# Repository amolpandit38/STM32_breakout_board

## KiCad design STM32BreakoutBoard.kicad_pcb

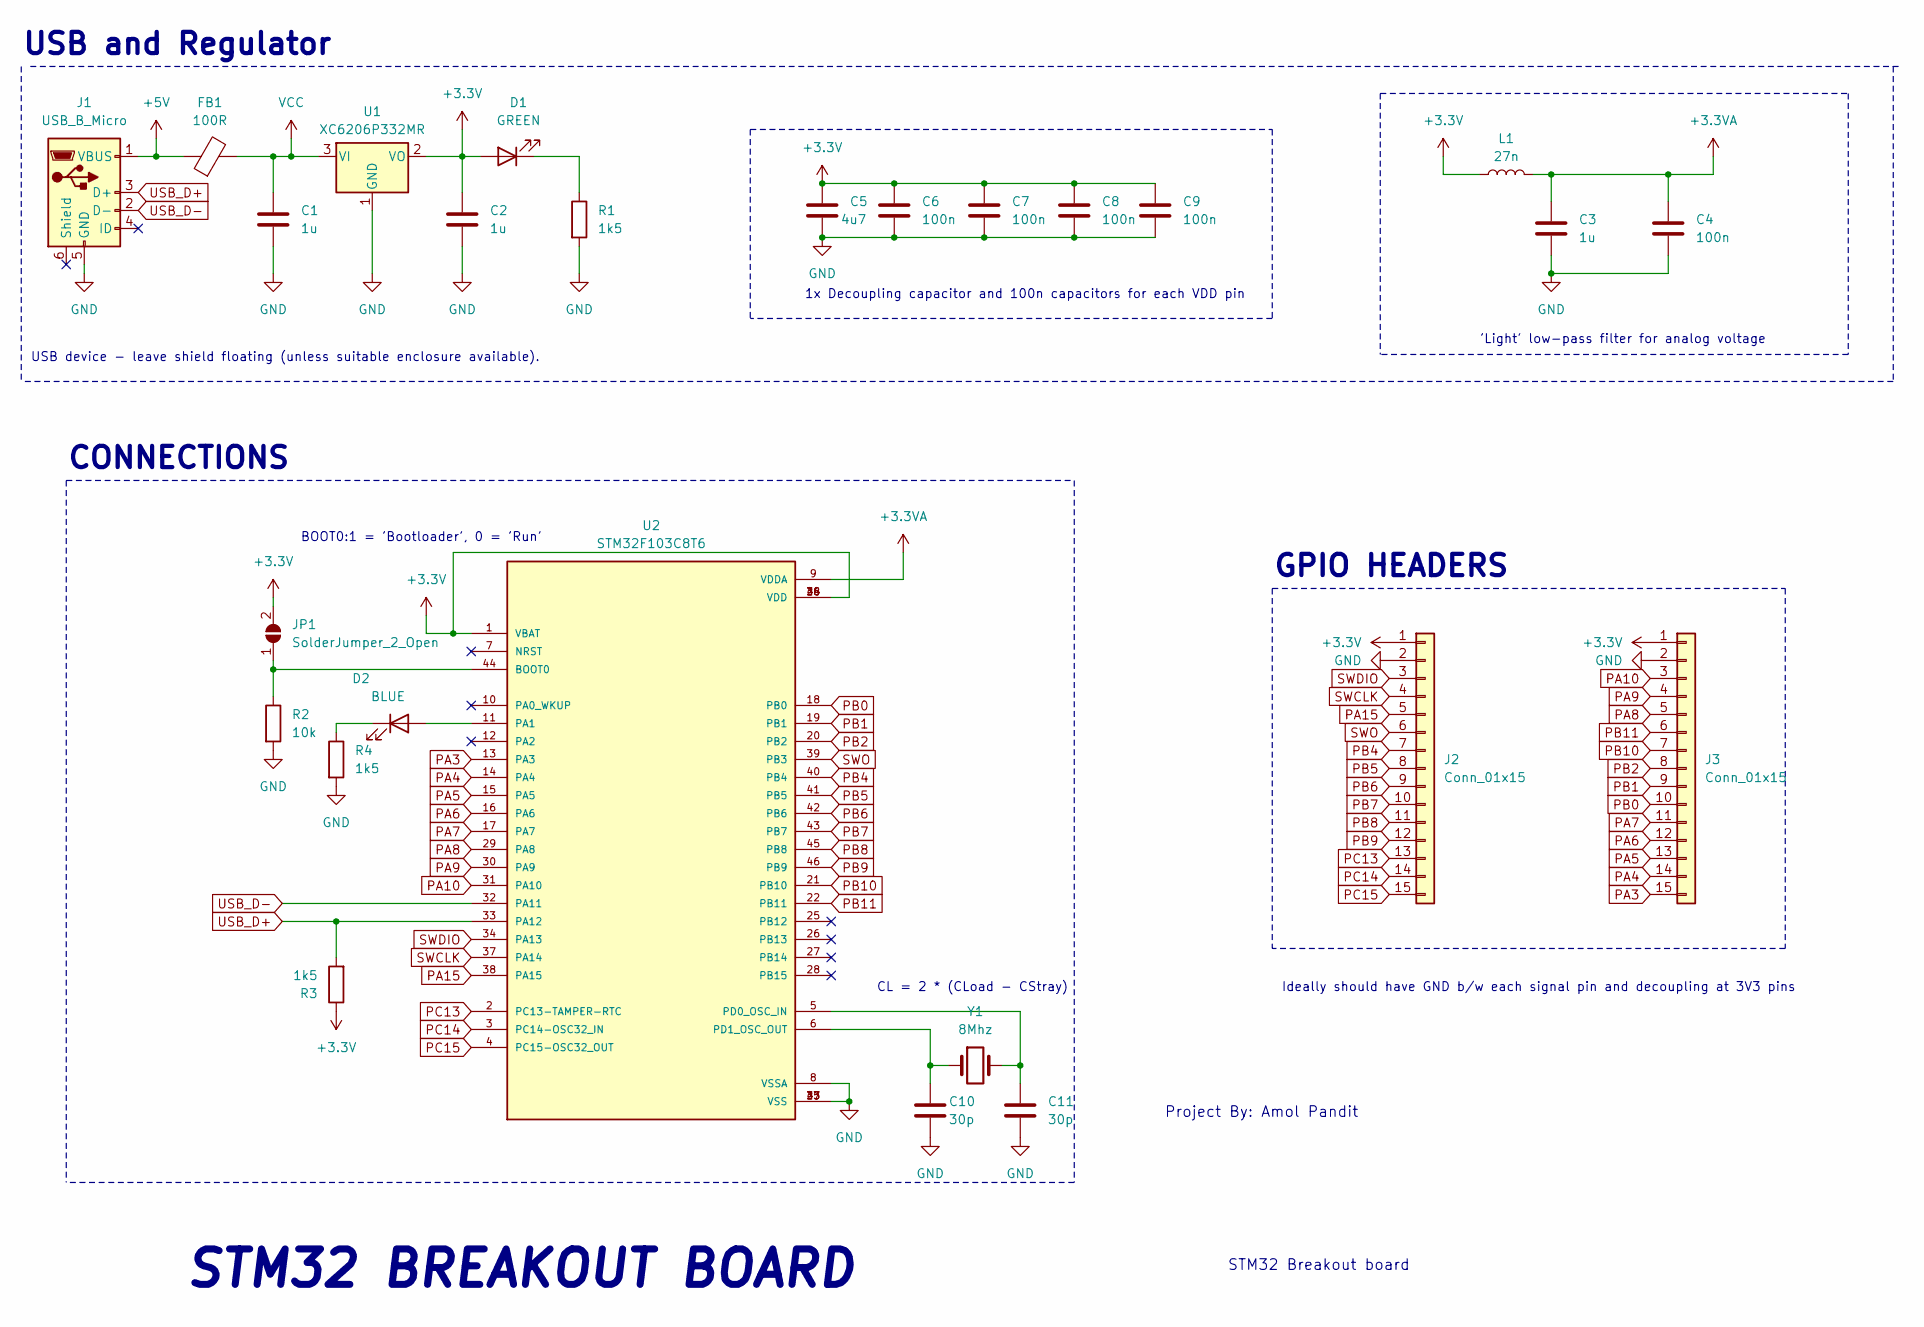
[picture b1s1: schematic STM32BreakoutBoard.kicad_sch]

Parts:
C1, C2, C3: 1u; C_0603_1608Metric
C4, C6, C7, C8, C9: 100n; C_0402_1005Metric
C5: 4u7; C_0603_1608Metric
C10, C11: 30p; C_0402_1005Metric
D1: GREEN; LED_0603_1608Metric
D2: BLUE; LED_0603_1608Metric
FB1: 100R; L_0805_2012Metric
J1: USB_B_Micro; USB_Micro-B_Wuerth_629105150521
J2, J3: Conn_01x15; PinHeader_1x15_P2.54mm_Vertical
JP1: SolderJumper_2_Open; SolderJumper-2_P1.3mm_Open_Pad1.0x1.5mm
L1: 27n; L_0402_1005Metric
R1, R3, R4: 1k5; R_0402_1005Metric
R2: 10k; R_0603_1608Metric
U1: XC6206P332MR; SOT-23-3
U2: STM32F103C8T6; QFP50P900X900X160-48N; PARTREV 10
Y1: 8Mhz; Crystal_SMD_5032-2Pin_5.0x3.2mm

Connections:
+3.3V: C2.1, C5.1, C6.1, C7.1, C8.1, C9.1, D1.2 (A), J2.1, J3.1, JP1.2 (B), L1.1, R3.1, U1.2 (VO), U2.1 (VBAT), U2.24 (VDD), U2.36 (VDD), U2.48 (VDD)
+3.3VA: C3.1, C4.1, L1.2, U2.9 (VDDA)
+5V: FB1.1, J1.1 (VBUS)
GND: C1.2, C2.2, C3.2, C4.2, C5.2, C6.2, C7.2, C8.2, C9.2, C10.2, C11.2, J1.5 (GND), J2.2, J3.2, R1.2, R2.2, R4.2, U1.1 (GND), U2.8 (VSSA), U2.23 (VSS), U2.35 (VSS), U2.47 (VSS)
unnamed: D1.1 (K), R1.1
unnamed: D2.2 (A), U2.11 (PA1)
unnamed: D2.1 (K), R4.1
unnamed: JP1.1 (A), R2.1, U2.44 (BOOT0)
unnamed: C11.1, U2.5 (PD0_OSC_IN), Y1.2
unnamed: C10.1, U2.6 (PD1_OSC_OUT), Y1.1
PA3: J3.15, U2.13 (PA3)
PA4: J3.14, U2.14 (PA4)
PA5: J3.13, U2.15 (PA5)
PA6: J3.12, U2.16 (PA6)
PA7: J3.11, U2.17 (PA7)
PA8: J3.5, U2.29 (PA8)
PA9: J3.4, U2.30 (PA9)
PA10: J3.3, U2.31 (PA10)
PA15: J2.5, U2.38 (PA15)
PB0: J3.10, U2.18 (PB0)
PB1: J3.9, U2.19 (PB1)
PB2: J3.8, U2.20 (PB2)
PB4: J2.7, U2.40 (PB4)
PB5: J2.8, U2.41 (PB5)
PB6: J2.9, U2.42 (PB6)
PB7: J2.10, U2.43 (PB7)
PB8: J2.11, U2.45 (PB8)
PB9: J2.12, U2.46 (PB9)
PB10: J3.7, U2.21 (PB10)
PB11: J3.6, U2.22 (PB11)
PC13: J2.13, U2.2 (PC13-TAMPER-RTC)
PC14: J2.14, U2.3 (PC14-OSC32_IN)
PC15: J2.15, U2.4 (PC15-OSC32_OUT)
SWCLK: J2.4, U2.37 (PA14)
SWDIO: J2.3, U2.34 (PA13)
SWO: J2.6, U2.39 (PB3)
USB_D+: J1.3 (D+), R3.2, U2.33 (PA12)
USB_D-: J1.2 (D-), U2.32 (PA11)
VCC: C1.1, FB1.2, U1.3 (VI)

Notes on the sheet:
Ideally should have GND b/w each signal pin and decoupling at 3V3 pins
USB device - leave shield floating (unless suitable enclosure available).
GPIO HEADERS
STM32 BREAKOUT BOARD
USB and Regulator
1x Decoupling capacitor and 100n capacitors for each VDD pin
BOOT0:1 = 'Bootloader', 0 = 'Run'
STM32 Breakout board
CL = 2 * (CLoad - CStray)
Project By: Amol Pandit
'Light' low-pass filter for analog voltage
CONNECTIONS

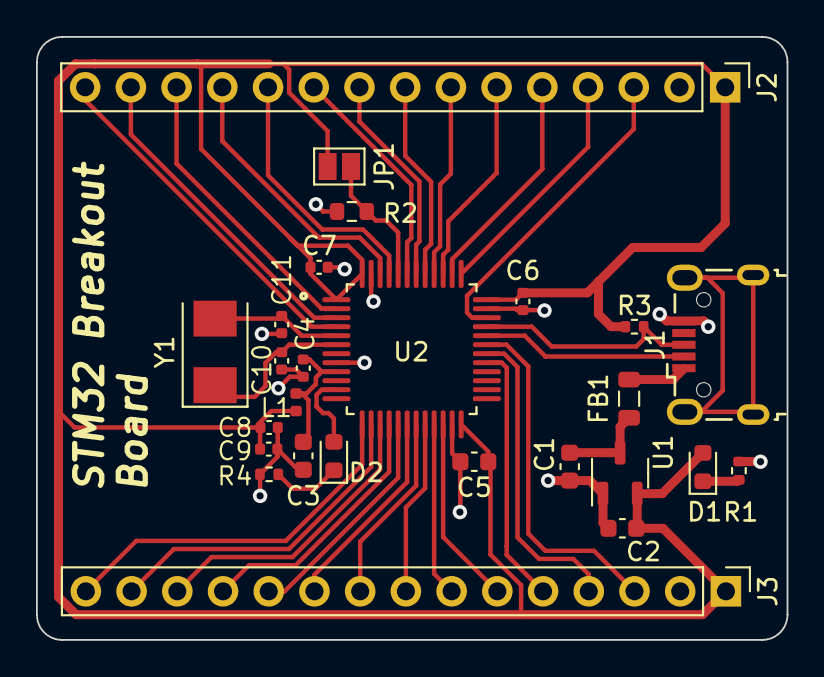
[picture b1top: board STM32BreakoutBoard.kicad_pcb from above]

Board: 2 copper layers, 41.7 x 33.5 mm, 26 parts (0 on the bottom side), 39 nets.

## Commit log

2023-12-09 Adding files for STM32 breakout board includes sch and pch layout
